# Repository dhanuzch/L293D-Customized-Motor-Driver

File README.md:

# L293D Motor Driver
This repo consists of a L293D based motor driver compatible with microcontrollers. The main motivation behind this project was because of unavailability of a motor driver that exactly fits in a custom made robot.

## Using Gerber file
Just upload/give this file to online board houses such as JLCPCB or offline board houses, if you are intereseted in printing this PCB.

## Files
 - **[Board](https://github.com/dhanuzch/L293D-Customized-Motor-Driver/edit/master/Board/)** consists of eagle *project, schematic and board files*
 - **[Images](https://github.com/dhanuzch/L293D-Customized-Motor-Driver/edit/master/Images/)** of board and schematics
 - **L293D_gerber.zip** pre-zipped so it is easy to print the PCBs

## Parts List
|Quantity         |Component Name | Name in schematics|                        
|----------------|---------------|---|
|1|L293D TH |**IC1**|
|2|LM317M SMD|**IC3**|
|3|1N4002|**D1**|
|4|1N4002|**D2**|
|5|240ohms SMD|**R1** |
|6|720ohms SMD|**R2** |
|7|0.1uF TH|**C3**|
|8|1uF SMD|**C4** |
|9|10uF SMD|**C5**|
|10|Connectors-KF301|**X1**|

## Specs
|         |Min | Max |Unit|                        
|----------------|-----|----|---|
|Input voltage(Vcc1)|4.5|7|V|
|Input voltage(Vcc2)|4.5|36|V|
|Output current|-1|1|A|
|Operating temperature|0|70|°C|

*Vcc1* -  Voltage for internal logic translation<br>
*Vcc2* -  Voltage for drivers

It is also advisable to use heatsink to increase the lifespan of the IC.

## Disclaimer
Using an offshelf L298N motor driver is a better option if you are dealing with motors that use more than 1A current.

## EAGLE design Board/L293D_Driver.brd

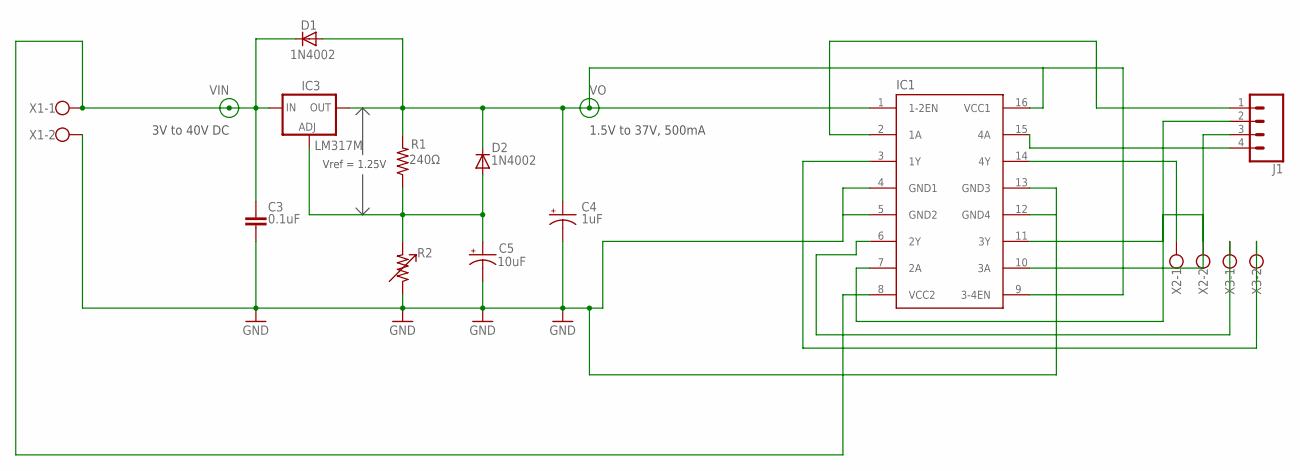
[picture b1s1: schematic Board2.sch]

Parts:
C3: 0.1uF; C075-052X106
C4: 1uF; 085CS_1AR
C5: 10uF; 085CS_1AR
D1, D2: 1N4002; DO41-10
IC1: L293D; DIL16
IC3: LM317MBSTT3; SOT223; PARTNUMBER LM317M
J1: CONN_04PTH; 1X04
R1: 240Ω; M0805
R2: RESISTOR_TRIMR0805; R0805
X1, X2, X3: W237-102

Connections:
GND: C3.2, C4.-, C5.-, IC1.4 (GND1), IC1.5 (GND2), IC1.12 (GND4), IC1.13 (GND3), R2.1, X1.2
unnamed: C5.+, D2.A, IC3.1 (ADJ), R1.1, R2.2
unnamed: IC1.15 (4A), J1.4
unnamed: IC1.10 (3A), J1.3
unnamed: IC1.14 (4Y), X2.1
unnamed: IC1.11 (3Y), X2.2
unnamed: IC1.3 (1Y), X3.2
unnamed: IC1.6 (2Y), X3.1
unnamed: IC1.7 (2A), J1.2
unnamed: IC1.2 (1A), J1.1
VIN: C3.1, D1.C, IC1.8 (VCC2), IC3.3 (IN), X1.1
VO: C4.+, D1.A, D2.C, IC1.1 (1-2EN), IC1.9 (3-4EN), IC1.16 (VCC1), IC3.4 (OUT), R1.2

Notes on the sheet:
Vref = 1.25V
3V to 40V DC
1.5V to 37V, 500mA

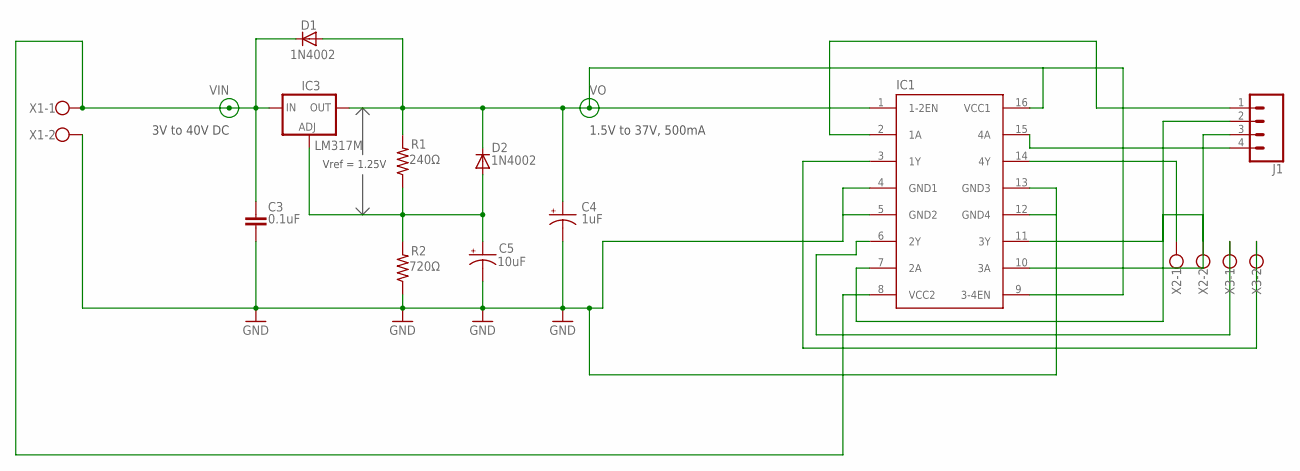
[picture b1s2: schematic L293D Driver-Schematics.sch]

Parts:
C3: 0.1uF; C075-052X106
C4: 1uF; 085CS_1AR
C5: 10uF; 085CS_1AR
D1, D2: 1N4002; DO41-10
IC1: L293D; DIL16
IC3: LM317MBSTT3; SOT223; PARTNUMBER LM317M
J1: CONN_04PTH; 1X04
R1: 240Ω; M0805
R2: 720Ω; M0805
X1, X2, X3: W237-102

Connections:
GND: C3.2, C4.-, C5.-, IC1.4 (GND1), IC1.5 (GND2), IC1.12 (GND4), IC1.13 (GND3), R2.1, X1.2
unnamed: C5.+, D2.A, IC3.1 (ADJ), R1.1, R2.2
unnamed: IC1.15 (4A), J1.4
unnamed: IC1.10 (3A), J1.3
unnamed: IC1.14 (4Y), X2.1
unnamed: IC1.11 (3Y), X2.2
unnamed: IC1.3 (1Y), X3.2
unnamed: IC1.6 (2Y), X3.1
unnamed: IC1.7 (2A), J1.2
unnamed: IC1.2 (1A), J1.1
VIN: C3.1, D1.C, IC1.8 (VCC2), IC3.3 (IN), X1.1
VO: C4.+, D1.A, D2.C, IC1.1 (1-2EN), IC1.9 (3-4EN), IC1.16 (VCC1), IC3.4 (OUT), R1.2

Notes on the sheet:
Vref = 1.25V
3V to 40V DC
1.5V to 37V, 500mA

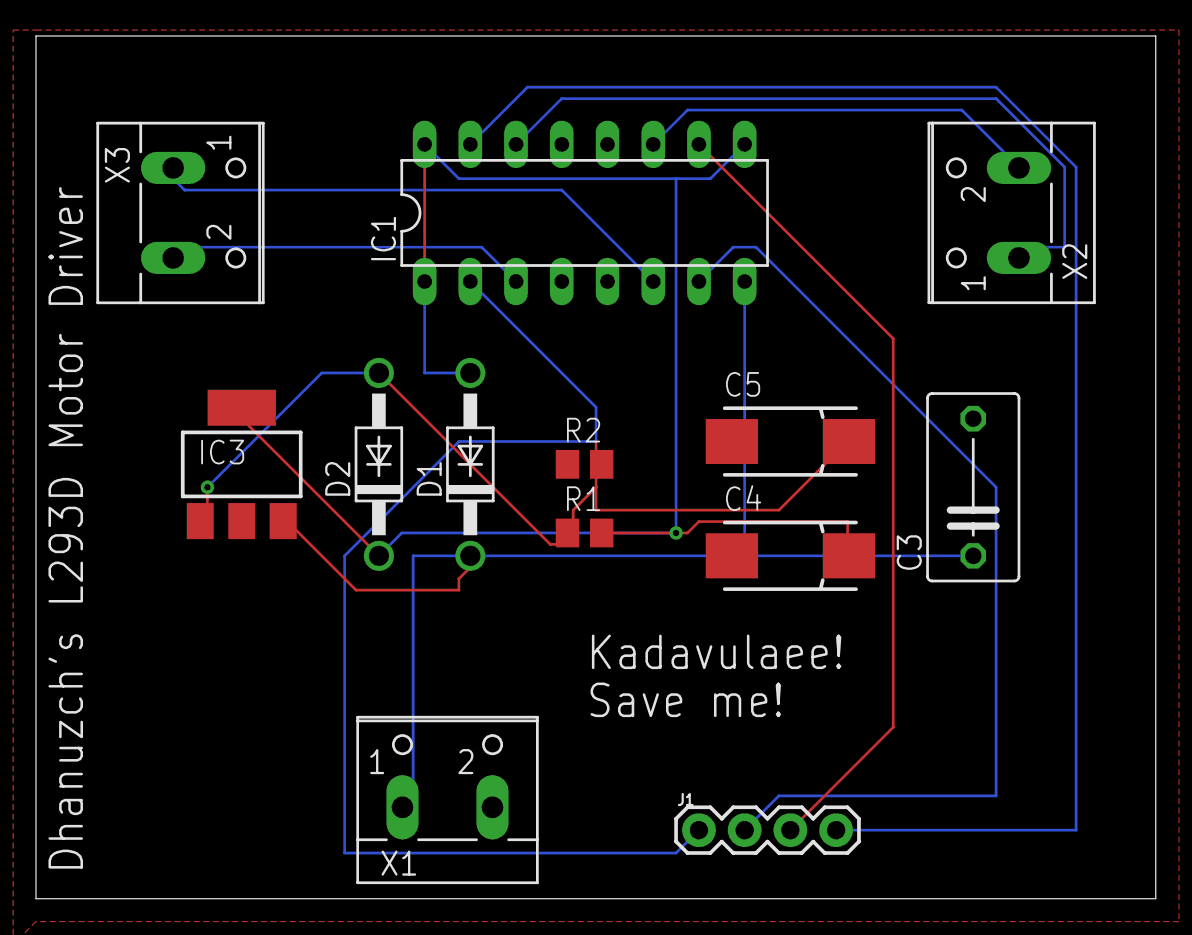
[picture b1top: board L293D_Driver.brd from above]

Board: 2 copper layers, 62.2 x 47.9 mm, 13 parts (0 on the bottom side), 12 nets.

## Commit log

2020-08-28 Added Files
2020-08-28 Use this when ordering PCB
2020-08-28 Deleted repaeated files and Renamed
2020-08-28 Updated resistor value for 5V
2020-08-28 Changed Resistor Values
2020-08-28 Resized Image & Altered Board
2020-08-28 Resized
2020-08-28 Resized Images
2020-09-01 Renamed
2020-09-01 Regenerated Gerber Files
2020-09-01 Deleted Old
2020-09-01 Gerber modified
2020-11-05 Renamed and added images

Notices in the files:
parts and their libraries:
SparkFun-Connectors: Licensing: Creative Commons ShareAlike 4.0 International - https://creativecommons.org/licenses/by-sa/4.0
